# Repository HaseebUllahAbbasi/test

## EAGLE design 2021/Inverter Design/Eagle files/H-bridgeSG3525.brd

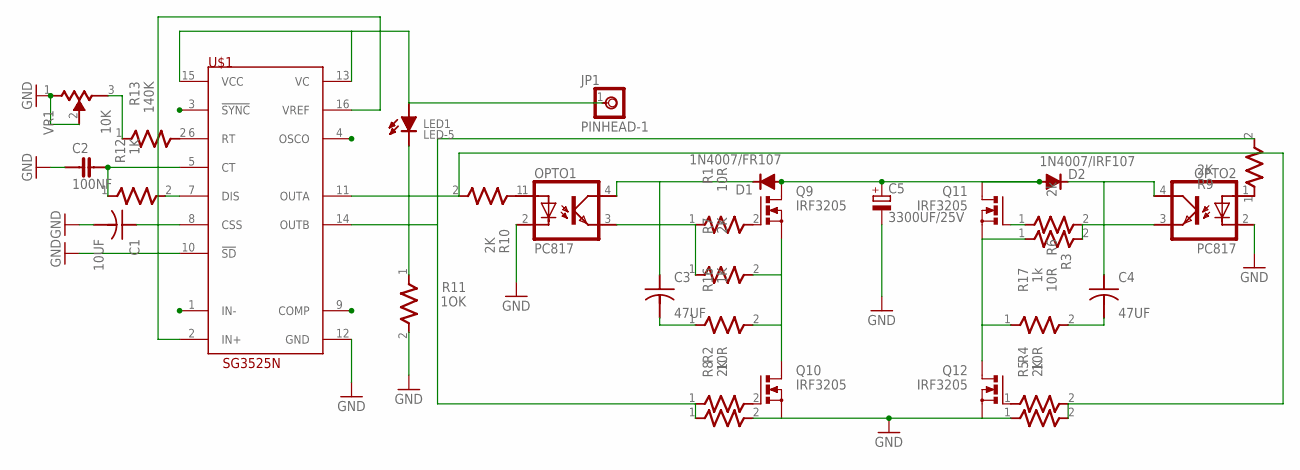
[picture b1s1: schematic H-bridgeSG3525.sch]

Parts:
C1: 10UF; CAP-2,5
C2: 100NF; CAP-NP5
C3, C4: 47UF; CAP-2,5
C5: 3300UF/25V; E7,5-18
D1: 1N4007/FR107; 1N4007
D2: 1N4007/IRF107; 1N4007
JP1: PINHEAD-1
LED1: LED-5; LED5
OPTO1, OPTO2: PC817; DIL-04
Q9, Q10, Q11, Q12: IRF3205; TO220BV
R1, R2, R3, R4: 10R; R-7,5
R5, R7, R8, R9, R10: 2K; R-7,5
R6: 2k; R-7,5
R11: 1OK; R-7,5
R12, R16: 1K; R-7,5
R13: 140K; R-7,5
R17: 1k; R-7,5
U$1: SG3525N; DIL16
VR1: 10K; VR-5

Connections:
12V: C5.+, D1.A, D2.A, Q9.D, Q11.D
COMP: U$1.9 (COMP)
CSS: C1.+ (1), U$1.8 (CSS)
GND: C1.- (2), C2.1, C5.-, OPTO1.2 (C), OPTO2.2 (C), Q10.S, Q12.S, R5.1, R8.2, R11.2, U$1.10 (!SD), U$1.12 (GND), VR1.1, VR1.2
IN-: U$1.1 (IN-)
unnamed: Q9.S, Q10.D, R7.2, R16.2
unnamed: C3.+ (1), D1.K, OPTO1.4 (COL)
unnamed: C4.+ (1), D2.K, OPTO2.4 (COL)
unnamed: OPTO1.3 (EMI), R1.1, R7.1
unnamed: OPTO2.3 (EMI), R3.2, R6.2
unnamed: OPTO2.1 (A), R9.1
unnamed: R13.1, VR1.3
unnamed: OPTO1.1 (A), R10.1
unnamed: LED1.K, R11.1
unnamed: C3.- (2), R16.1
unnamed: R12.2, U$1.7 (DIS)
unnamed: C4.- (2), R17.2
unnamed: R13.2, U$1.6 (RT)
unnamed: Q11.S, Q12.D, R6.1, R17.1
unnamed: Q9.G, R1.2
unnamed: Q10.G, R2.2
unnamed: Q11.G, R3.1
unnamed: Q12.G, R4.1
unnamed: C2.2, R12.1, U$1.5 (CT)
OUTA: R4.2, R5.2, R10.2, U$1.11 (OUTA)
OUTB: R2.1, R8.1, R9.2, U$1.14 (OUTB)
VCC: JP1.1, LED1.A, U$1.13 (VC), U$1.15 (VCC)
VREF: U$1.2 (IN+), U$1.16 (VREF)

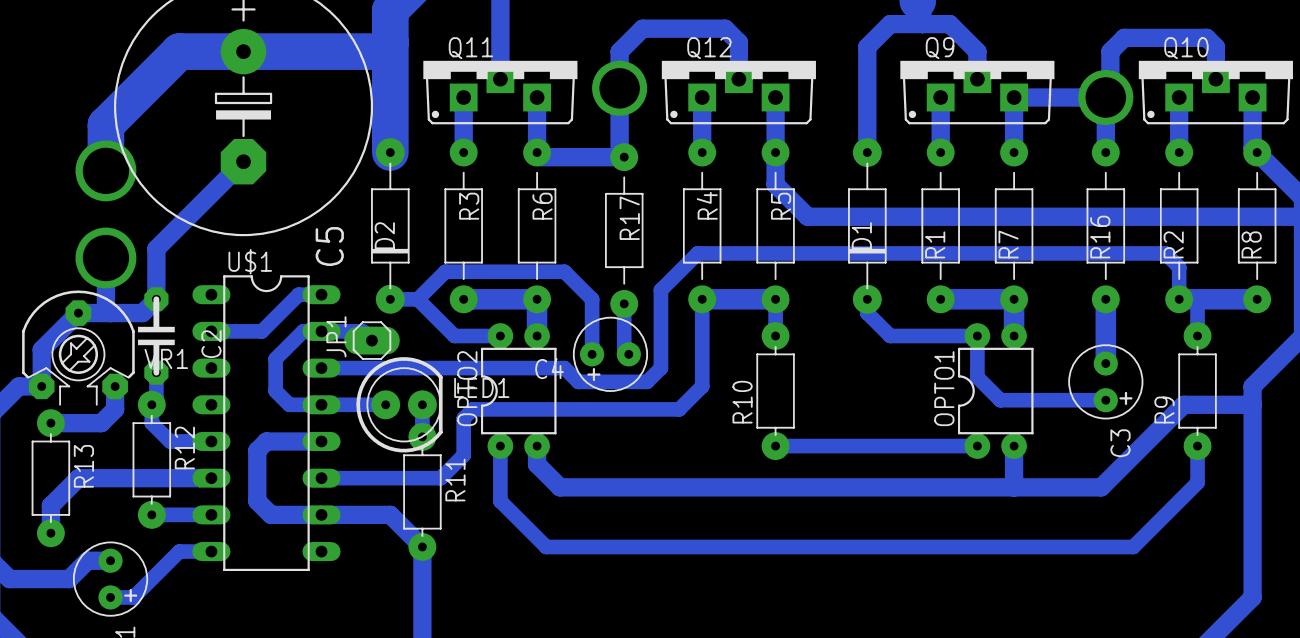
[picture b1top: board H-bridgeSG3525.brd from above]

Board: 2 copper layers, 32 parts (0 on the bottom side), 26 nets.

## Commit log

2021-10-14 added changes
2021-10-14 changes made in the extension 1
2021-10-14 Changes made in the extention 2
2021-10-14 added changes 1
2021-10-14 init 2021
2021-10-14 changed extension
2021-10-14 added project
2021-10-14 inverter design
